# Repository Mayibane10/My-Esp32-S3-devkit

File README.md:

# My-Esp32-S3-devkit

This is a custom made esp32 development board that is designed for IoT uses with a bunch of capabilities

---

Feel free to make changes to the schematic design
this is just the schematic and PCB design, and ill make some example code libraries some time in the future

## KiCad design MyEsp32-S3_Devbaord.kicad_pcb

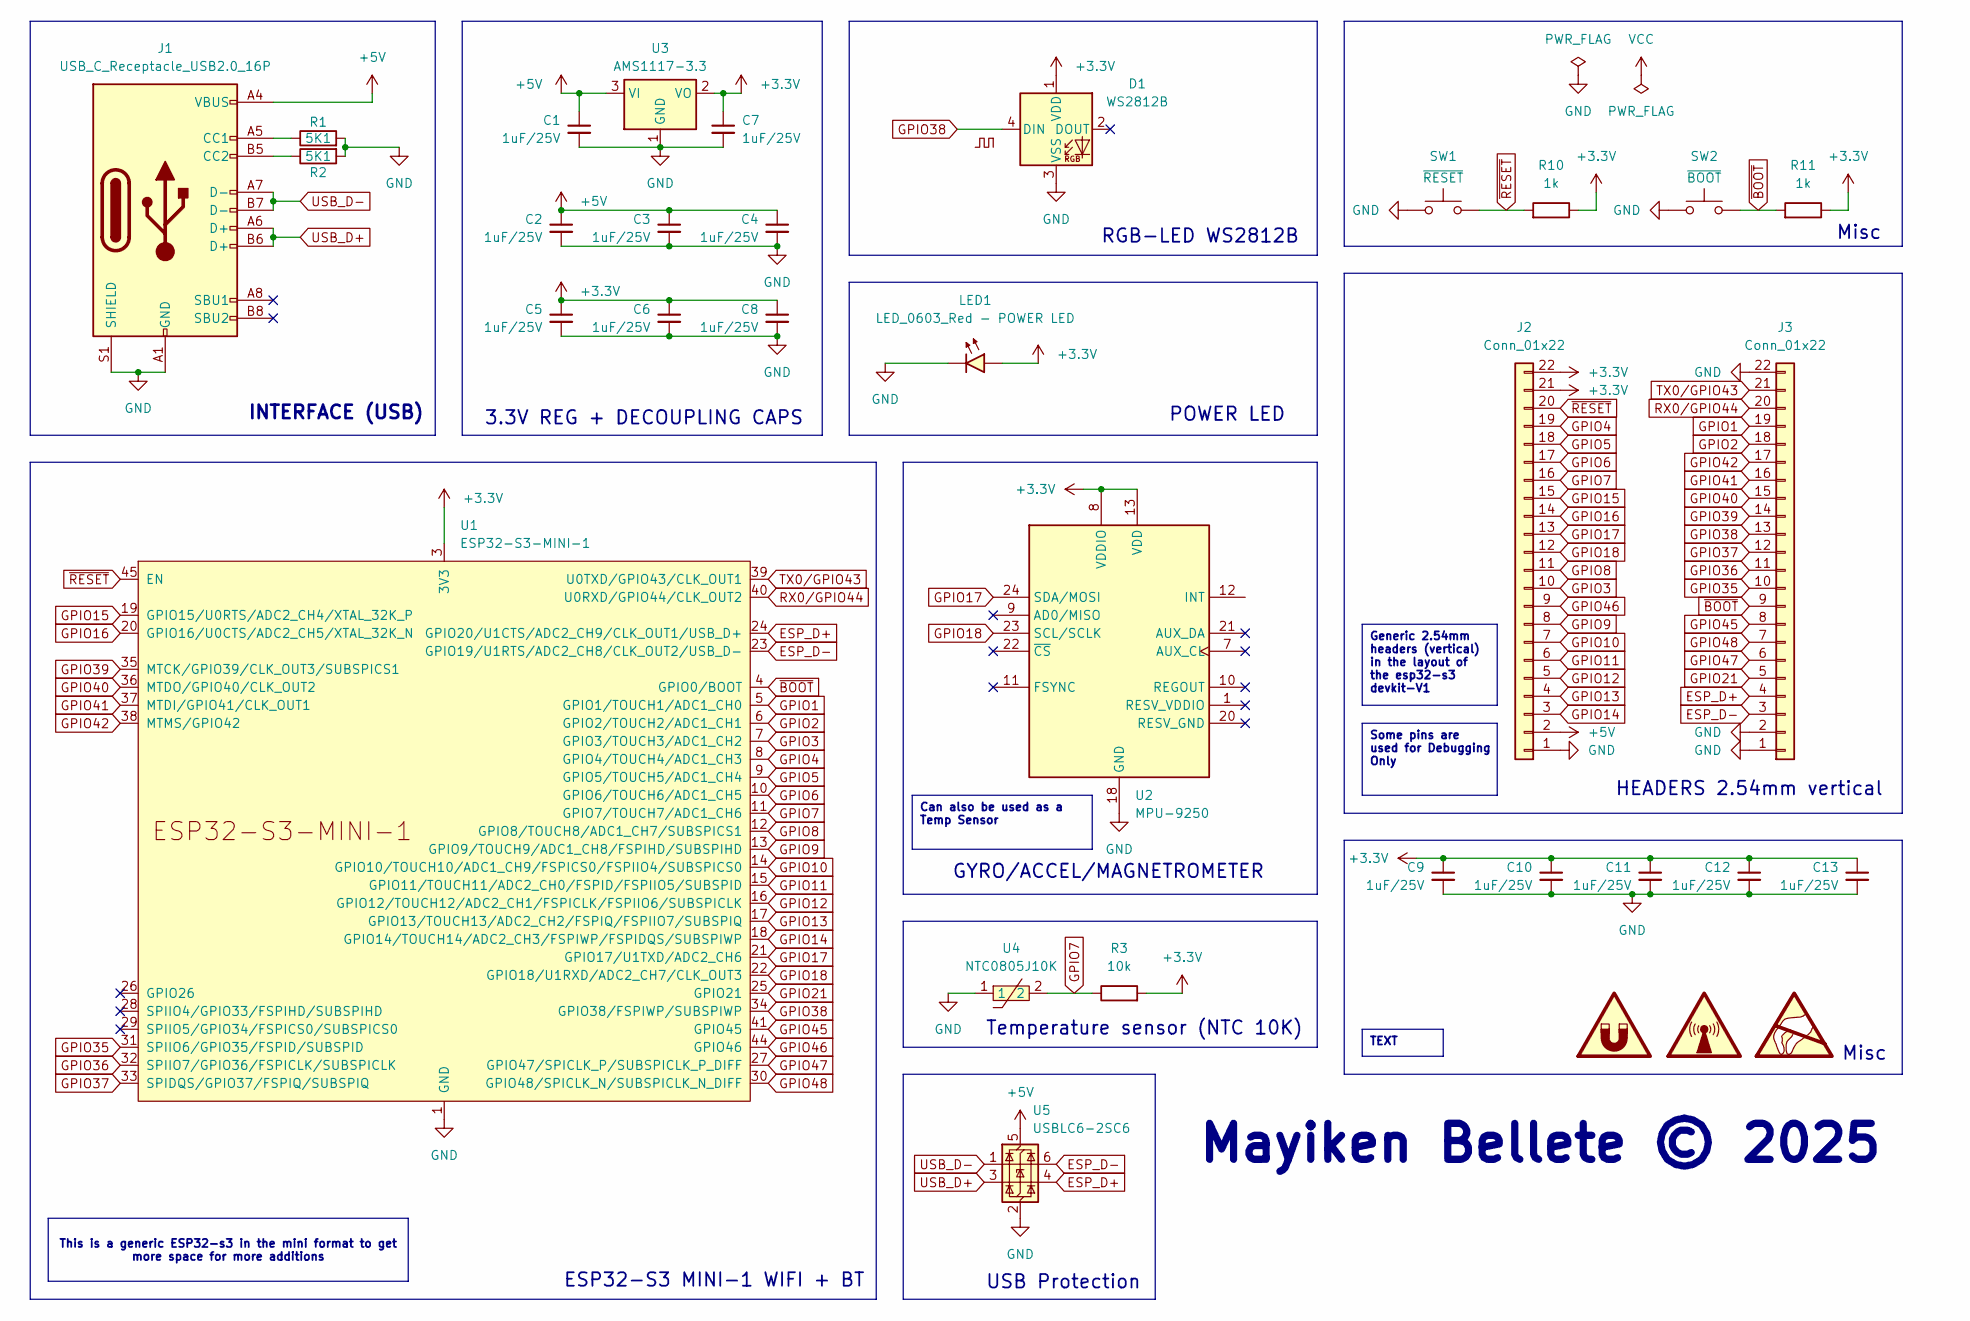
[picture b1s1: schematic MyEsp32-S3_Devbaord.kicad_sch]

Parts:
C1, C2, C3, C4, C5, C6, C7, C8, C9, C10, C11, C12, C13: 1uF_0603_25V; C_0603_1608Metric; Part Number GRM188R61E105KA12D; JLCPCB ID C15849
D1: WS2812B; LED_WS2812B_PLCC4_5.0x5.0mm_P3.2mm
J1: USB_C_Receptacle_USB2.0_16P; USB_C_Receptacle_GCT_USB4105-xx-A_16P_TopMnt_Horizontal
J2, J3: Conn_01x22; PinHeader_1x22_P2.54mm_Vertical
LED1: LED_0603_Red - POWER LED; LED_0603_1608Metric
R1, R2: 5K1; R_0603_1608Metric; LCSC Part C2907044
R3: 10k_0603; R_0603_1608Metric; Part Number RC0603FR-0710KL; JLCPCB ID C25804
R10, R11: 1k_0603; R_0603_1608Metric; Part Number RC0603FR-071KL; JLCPCB ID C21190
SW1: ~{RESET}; SW_SPST_B3U-1000P
SW2: ~{BOOT}; SW_SPST_B3U-1000P
U1: ESP32-S3-MINI-1; ESP32-S2-MINI-1
U2: MPU-9250; InvenSense_QFN-24_3x3mm_P0.4mm
U3: AMS1117-3.3; SOT-223-3_TabPin2
U4: NTC0805J10K; R0805; LCSC Part C17376775
U5: USBLC6-2SC6; SOT-23-6
U6: Square_Small

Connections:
+3.3V: C5.1, C6.1, C7.1, C8.1, C9.1, C10.1, C11.1, C12.1, C13.1, D1.1 (VDD), J2.21, J2.22, LED1.2 (A), R3.2, R10.1, R11.1, U1.3 (3V3), U2.8 (VDDIO), U2.13 (VDD), U3.2 (VO)
+5V: C1.1, C2.1, C3.1, C4.1, J1.A4 (VBUS), J1.A9 (VBUS), J1.B4 (VBUS), J1.B9 (VBUS), J2.2, U3.3 (VI), U5.5 (VBUS)
ESP_D+: J3.4, U1.24 (GPIO20/U1CTS/ADC2_CH9/CLK_OUT1/USB_D+), U5.4 (I/O2)
ESP_D-: J3.3, U1.23 (GPIO19/U1RTS/ADC2_CH8/CLK_OUT2/USB_D-), U5.6 (I/O1)
GND: C1.2, C2.2, C3.2, C4.2, C5.2, C6.2, C7.2, C8.2, C9.2, C10.2, C11.2, C12.2, C13.2, D1.3 (VSS), J1.A1 (GND), J1.A12 (GND), J1.B1 (GND), J1.B12 (GND), J1.S1 (SHIELD), J2.1, J3.1, J3.2, J3.22, LED1.1 (K), R1.2, R2.2, SW1.1, SW2.1, U1.1 (GND), U1.2 (GND), U1.42 (GND), U1.43 (GND), U1.46 (GND), U1.47 (GND), U1.48 (GND), U1.49 (GND), U1.50 (GND), U1.51 (GND), U1.52 (GND), U1.53 (GND), U1.54 (GND), U1.55 (GND), U1.56 (GND), U1.57 (GND), U1.58 (GND), U1.59 (GND), U1.60 (GND), U1.61 (GND), U1.62 (GND), U1.63 (GND), U1.64 (GND), U1.65 (GND), U2.18 (GND), U3.1 (GND), U4.1, U5.2 (GND)
GPIO1: J3.19, U1.5 (GPIO1/TOUCH1/ADC1_CH0)
GPIO2: J3.18, U1.6 (GPIO2/TOUCH2/ADC1_CH1)
GPIO3: J2.10, U1.7 (GPIO3/TOUCH3/ADC1_CH2)
GPIO4: J2.19, U1.8 (GPIO4/TOUCH4/ADC1_CH3)
GPIO5: J2.18, U1.9 (GPIO5/TOUCH5/ADC1_CH4)
GPIO6: J2.17, U1.10 (GPIO6/TOUCH6/ADC1_CH5)
GPIO7: J2.16, R3.1, U1.11 (GPIO7/TOUCH7/ADC1_CH6), U4.2
GPIO8: J2.11, U1.12 (GPIO8/TOUCH8/ADC1_CH7/SUBSPICS1)
GPIO9: J2.8, U1.13 (GPIO9/TOUCH9/ADC1_CH8/FSPIHD/SUBSPIHD)
GPIO10: J2.7, U1.14 (GPIO10/TOUCH10/ADC1_CH9/FSPICS0/FSPIIO4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)
GPIO11: J2.6, U1.15 (GPIO11/TOUCH11/ADC2_CH0/FSPID/FSPIIO5/S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)
GPIO12: J2.5, U1.16 (GPIO12/TOUCH12/ADC2_CH1/FSPICLK/FSPIIO6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)
GPIO13: J2.4, U1.17 (GPIO13/TOUCH13/ADC2_CH2/FSPIQ/FSPIIO7/S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)
GPIO14: J2.3, U1.18 (GPIO14/TOUCH14/ADC2_CH3/FSPIWP/FSPIDQS/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)
GPIO15: J2.15, U1.19 (GPIO15/U0RTS/ADC2_CH4/XTAL_32K_P)
GPIO16: J2.14, U1.20 (GPIO16/U0CTS/ADC2_CH5/XTAL_32K_N)
GPIO17: J2.13, U1.21 (GPIO17/U1TXD/ADC2_CH6), U2.24 (SDA/MOSI)
GPIO18: J2.12, U1.22 (GPIO18/U1RXD/ADC2_CH7/CLK_OUT3), U2.23 (SCL/SCLK)
GPIO21: J3.5, U1.25 (GPIO21)
GPIO35: J3.10, U1.31 (SPIIO6/GPIO35/FSPID/SUBSPID)
GPIO36: J3.11, U1.32 (SPIIO7/GPIO36/FSPICLK/SUBSPICLK)
GPIO37: J3.12, U1.33 (SPIDQS/GPIO37/FSPIQ/SUBSPIQ)
GPIO38: D1.4 (DIN), J3.13, U1.34 (GPIO38/FSPIWP/SUBSPIWP)
GPIO39: J3.14, U1.35 (MTCK/GPIO39/CLK_OUT3/SUBSPICS1)
GPIO40: J3.15, U1.36 (MTDO/GPIO40/CLK_OUT2)
GPIO41: J3.16, U1.37 (MTDI/GPIO41/CLK_OUT1)
GPIO42: J3.17, U1.38 (MTMS/GPIO42)
GPIO45: J3.8, U1.41 (GPIO45)
GPIO46: J2.9, U1.44 (GPIO46)
GPIO47: J3.6, U1.27 (GPIO47/SPICLK_P/SUBSPICLK_P_DIFF)
GPIO48: J3.7, U1.30 (GPIO48/SPICLK_N/SUBSPICLK_N_DIFF)
unnamed: J1.A5 (CC1), R1.1
unnamed: J1.B5 (CC2), R2.1
RX0/GPIO44: J3.20, U1.40 (U0RXD/GPIO44/CLK_OUT2)
TX0/GPIO43: J3.21, U1.39 (U0TXD/GPIO43/CLK_OUT1)
USB_D+: J1.A6 (D+), J1.B6 (D+), U5.3 (I/O2)
USB_D-: J1.A7 (D-), J1.B7 (D-), U5.1 (I/O1)
~BOOT: J3.9, R11.2, SW2.2, U1.4 (GPIO0/BOOT)
~RESET: J2.20, R10.2, SW1.2, U1.45 (EN)

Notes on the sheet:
3.3V REG + DECOUPLING CAPS
Misc
POWER LED
Temperature sensor (NTC 10K)
USB Protection
Mayiken Bellete © 2025
RGB-LED WS2812B
ESP32-S3 MINI-1 WIFI + BT
HEADERS 2.54mm vertical
INTERFACE (USB)
GYRO/ACCEL/MAGNETROMETER
Generic 2.54mm headers (vertical) in the layout of the esp32-s3 devkit-V1
This is a generic ESP32-s3 in the mini format to get more space for more additions
Can also be used as a Temp Sensor
Some pins are used for Debugging Only
TEXT

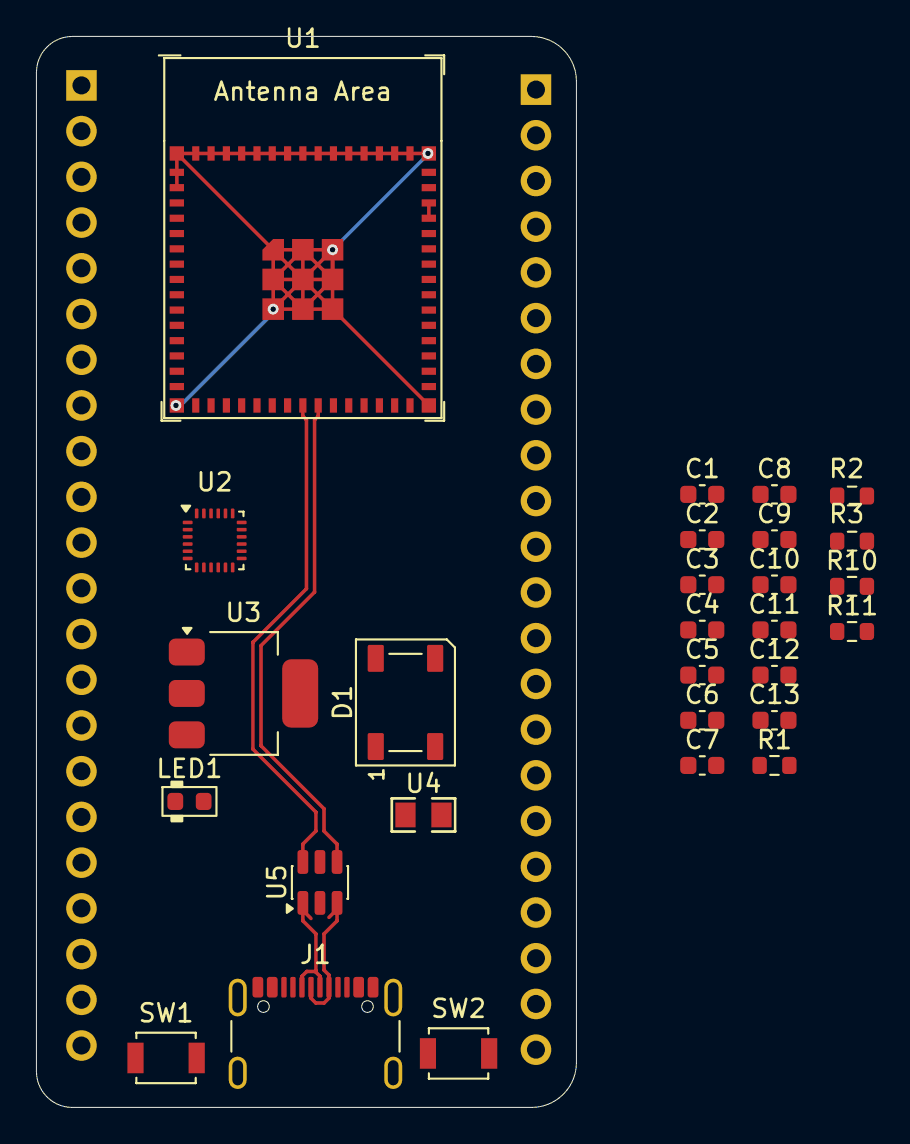
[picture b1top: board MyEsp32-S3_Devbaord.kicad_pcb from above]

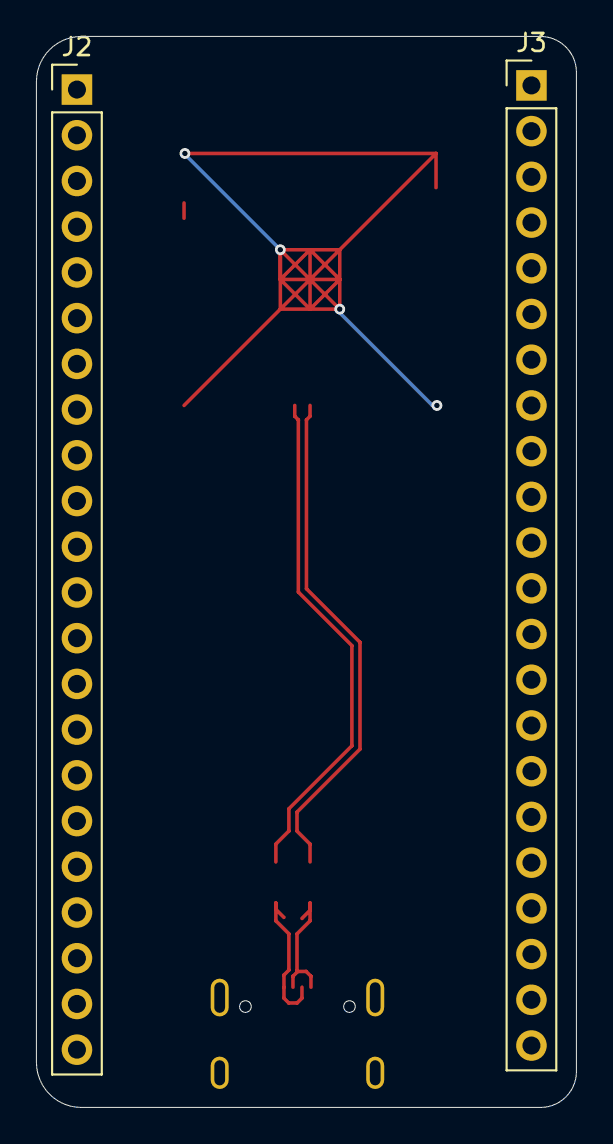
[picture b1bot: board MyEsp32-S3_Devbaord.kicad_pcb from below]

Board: 2 copper layers, 30.0 x 59.5 mm, 30 parts (2 on the bottom side), 44 nets.
